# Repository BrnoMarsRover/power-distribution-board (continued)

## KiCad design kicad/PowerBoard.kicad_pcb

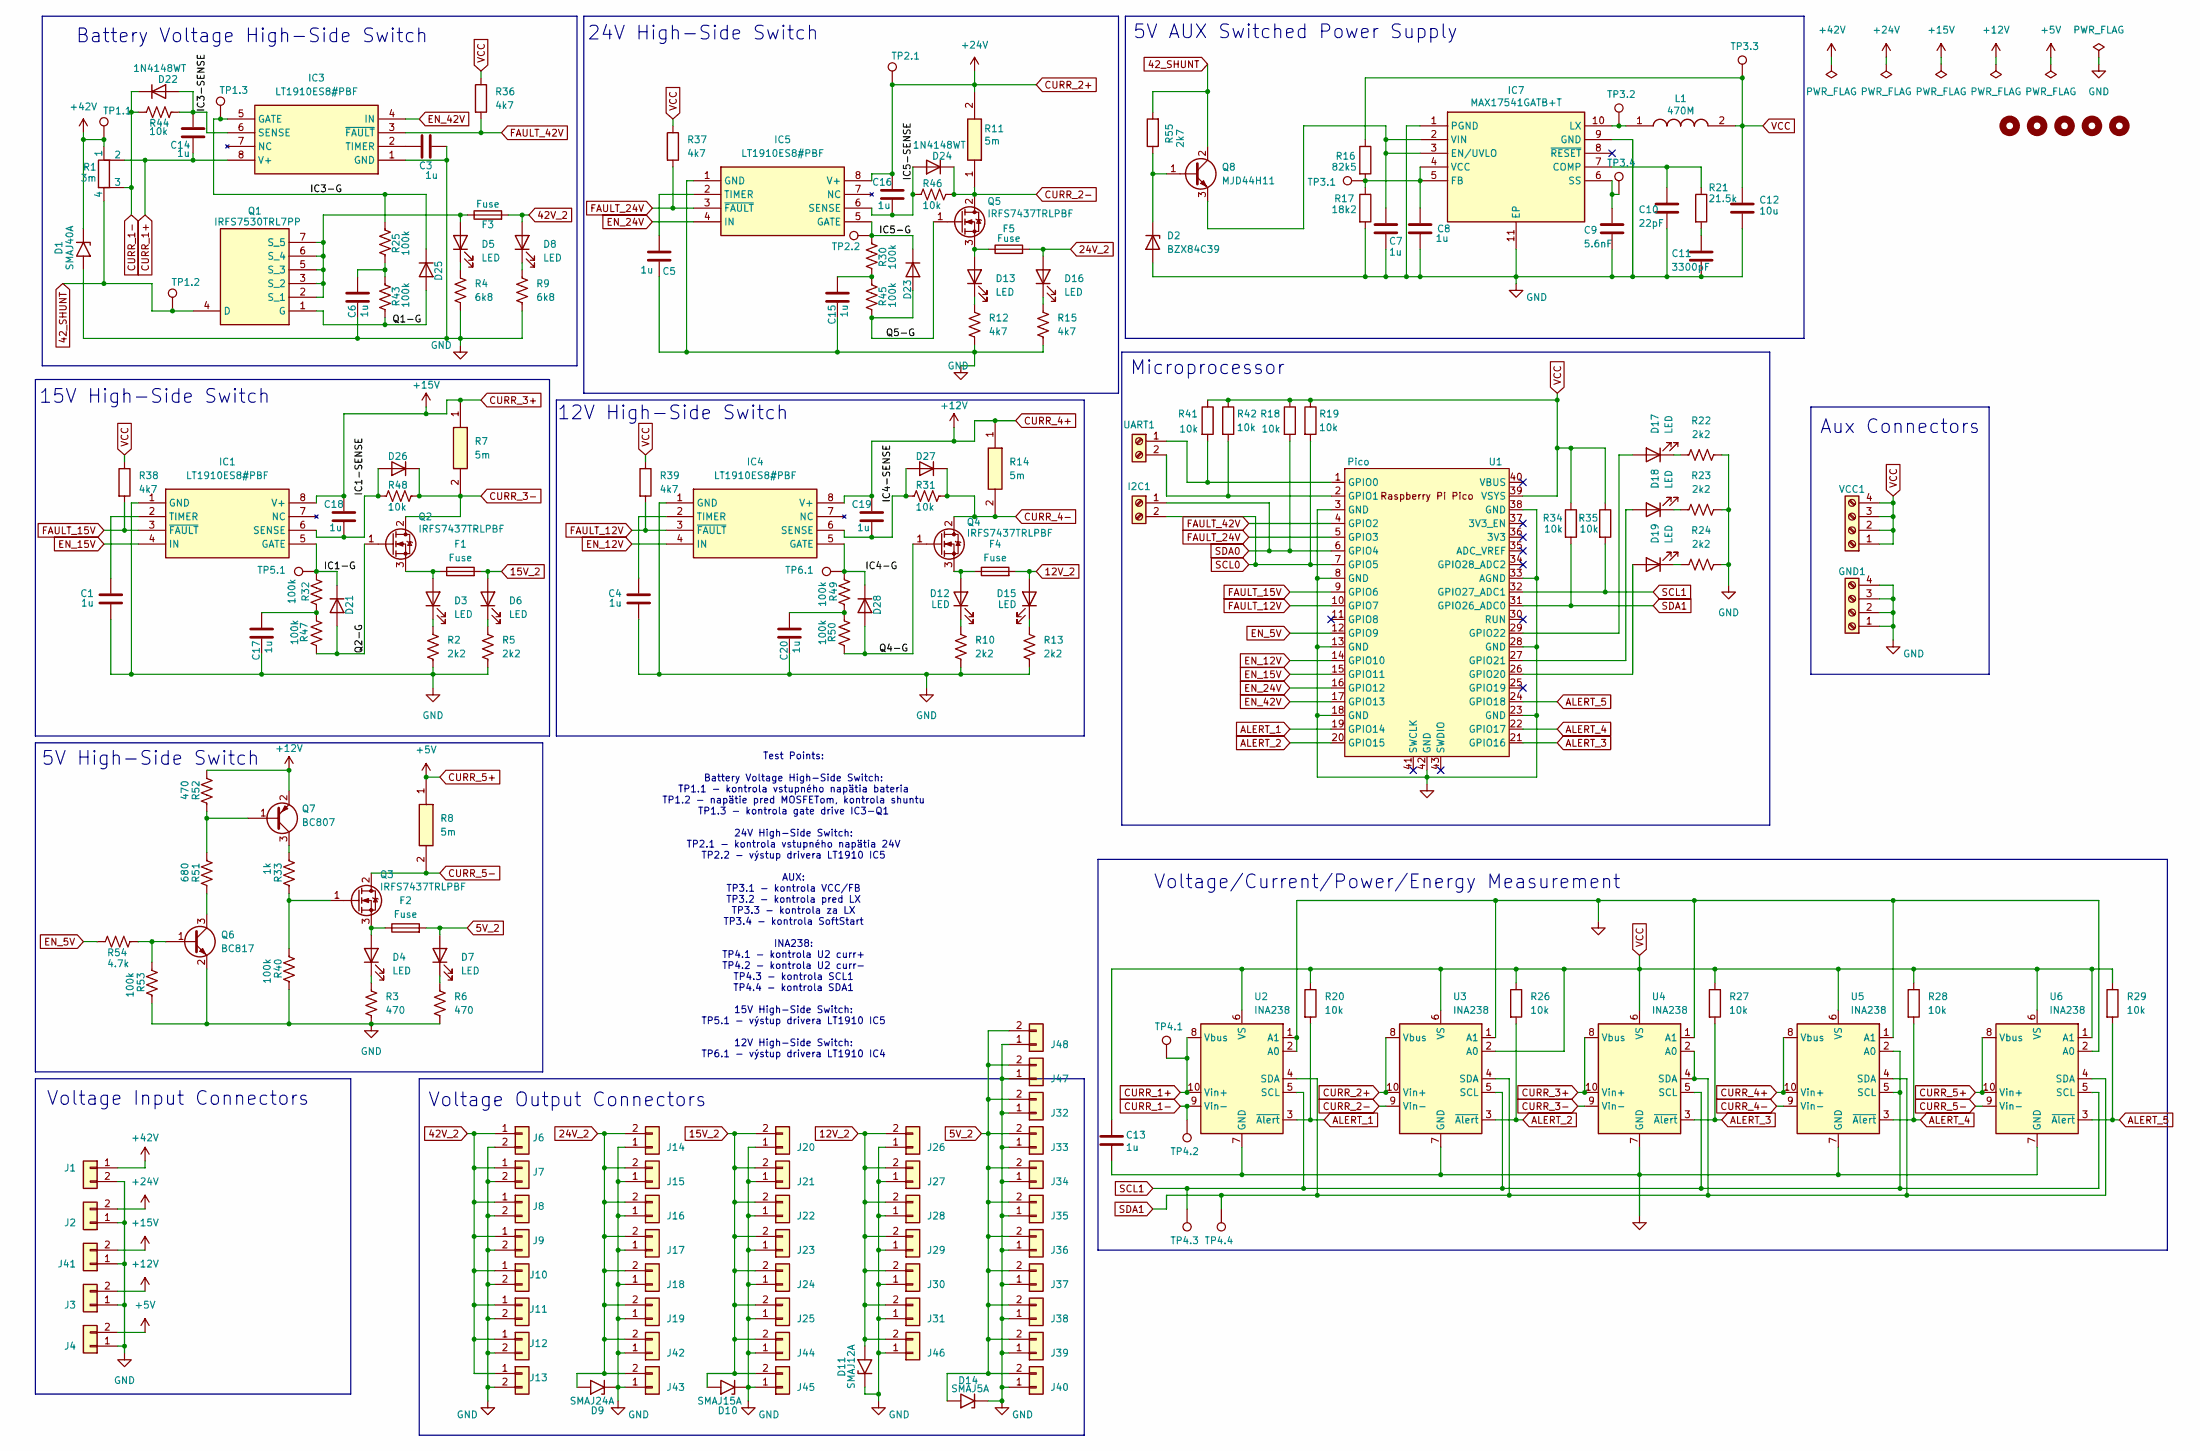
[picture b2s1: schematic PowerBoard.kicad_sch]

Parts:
C1, C3, C4, C5, C6, C7, C8, C14, C15, C16, C17, C18, C19, C20: 1u; C_0603_1608Metric
C9: 5.6nF; C_0603_1608Metric
C10: 22pF; C_0603_1608Metric
C11: 3300pF; C_0603_1608Metric
C12: 10u; C_0603_1608Metric
C13: 1u; C_1206_3216Metric
D1: SMAJ40A; D_SMA
D2: BZX84C39; SOT-23
D3, D4, D5, D6, D7, D8, D12, D13, D15, D16, D17, D18, D19: LED; D_1206_3216Metric
D9: SMAJ24A; D_SMA
D10: SMAJ15A; D_SMA
D11: SMAJ12A; D_SMA
D14: SMAJ5A; D_SMA
D21, D22, D23, D24, D25, D26, D27, D28: 1N4148WT; D_SOD-523
F1, F2, F3, F4, F5: Fuse; Fuse_Blade_ATO_directSolder
GND1: Screw_Terminal_01x04; TerminalBlock_Xinya_XY308-2.54-4P_1x04_P2.54mm_Horizontal
H1, H2, H3, H4, H5: MountingHole; MountingHole_3.2mm_M3
I2C1: Screw_Terminal_01x02; TerminalBlock_Xinya_XY308-2.54-2P_1x02_P2.54mm_Horizontal
IC1, IC3, IC4, IC5: LT1910ES8#PBF; SOIC127P599X175-8N; Mouser Part Number 584-LT1910ES8#PBF
IC7: MAX17541GATB+T; SON50P200X300X80-11N; Mouser Part Number 700-MAX17541GATB+T
J1, J6, J7, J8, J9, J10, J11, J12, J13: XT90
J2, J14, J15, J16, J17, J18, J19, J42, J43: DEAN_T; DEANS-T
J3, J20, J21, J22, J23, J24, J25, J26, J27, J28, J29, J30, J31, J41, J44, J45, J46: XT60; AMASS_XT60-F_1x02_P7.20mm_Vertical
J4, J32, J33, J34, J35, J36, J37, J38, J39, J40, J47, J48: XT30; AMASS_XT30U-F_1x02_P5.0mm_Vertical
L1: 470M; SRR5828A2R6Y; Mouser Part Number 6521-SRR5828A-470M
Q1: IRFS7530TRL7PP; Mouser Part Number 942-IRFS7530TRL7PP
Q2, Q3, Q4, Q5: IRFS7437TRLPBF; TO-263-2
Q6: BC817; SOT-23
Q7: BC807; SOT-23
Q8: MJD44H11; TO-252-2
R1: 3m; R_Shunt_Isabellenhuette_BVR4026
R2, R10: 2k2; R_0603_1608Metric
R3, R52: 470; R_0603_1608Metric
R4: 6k8; C_0603_1608Metric
R5, R13, R22, R23, R24: 2k2; R_1206_3216Metric
R6: 470; R_1206_3216Metric
R7, R8, R11, R14: 5m; RESC3216X89N; Mouser Part Number 71-WSL12061L000FEA
R9: 6k8; R_1206_3216Metric
R12: 4k7; R_0603_1608Metric
R15, R36, R37, R38, R39: 4k7; R_1206_3216Metric
R16: 82k5; R_0603_1608Metric
R17: 18k2; R_0603_1608Metric
R18, R19, R20, R26, R27, R28, R29, R34, R35, R41, R42: 10k; R_1206_3216Metric
R21: 21.5k; R_0603_1608Metric
R25, R30, R32, R40, R43, R45, R47, R49, R50, R53: 100k; R_0603_1608Metric
R31, R44, R46, R48: 10k; R_0603_1608Metric
R33: 1k; R_0603_1608Metric
R51: 680; R_0603_1608Metric
R54: 4.7k; R_0603_1608Metric
R55: 2k7; R_1206_3216Metric
TP1.1, TP1.2, TP1.3, TP2.1, TP2.2, TP3.1, TP3.2, TP3.3, TP3.4, TP4.1, TP4.2, TP4.3, TP4.4, TP5.1, TP6.1: TestPoint; TestPoint_Pad_1.0x1.0mm
U1: Pico; RPi_Pico_SMD_TH
U2, U3, U4, U5, U6: INA238; VSSOP-10_3x3mm_P0.5mm
UART1: Screw_Terminal_01x02; TerminalBlock_Xinya_XY308-2.54-2P_1x02_P2.54mm_Horizontal
VCC1: Screw_Terminal_01x04; TerminalBlock_Xinya_XY308-2.54-4P_1x04_P2.54mm_Horizontal

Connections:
5V_2: D7.2 (A), D14.2 (A2), F2.2, J32.2, J33.2, J34.2, J35.2, J36.2, J37.2, J38.2, J39.2, J40.2, J47.2, J48.2
12V_2: D11.2 (A2), D15.2 (A), F4.2, J26.2, J27.2, J28.2, J29.2, J30.2, J31.2, J46.2
15V_2: D6.2 (A), D10.2 (A2), F1.2, J20.2, J21.2, J22.2, J23.2, J24.2, J25.2, J44.2, J45.2
24V_2: D9.2 (A2), D16.2 (A), F5.2, J14.2, J15.2, J16.2, J17.2, J18.2, J19.2, J42.2, J43.2
42V_2: D8.2 (A), F3.2, J6.1, J7.1, J8.1, J9.1, J10.1, J11.1, J12.1, J13.1
42_SHUNT: Q1.4 (D), Q8.2 (C), R1.4, R55.2, TP1.2.1
+42V: D1.1 (A1), J1.1, R1.1, TP1.1.1
/IC1-G: D21.1 (K), IC1.5 (GATE), R32.2, TP5.1.1
/IC1-SENSE: C18.2, D26.2 (A), IC1.6 (SENSE), R48.1
/IC3-G: D25.1 (K), IC3.5 (GATE), R25.2, TP1.3.1
/IC3-SENSE: C14.1, D22.2 (A), IC3.6 (SENSE), R44.2
/IC4-G: D28.1 (K), IC4.5 (GATE), R49.2, TP6.1.1
/IC4-SENSE: C19.2, D27.2 (A), IC4.6 (SENSE), R31.1
/IC5-G: D23.1 (K), IC5.5 (GATE), R30.2, TP2.2.1
/IC5-SENSE: C16.2, D24.2 (A), IC5.6 (SENSE), R46.1
/Q1-G: D25.2 (A), Q1.1 (G), R43.2
/Q2-G: D21.2 (A), Q2.1 (G), R47.2
/Q4-G: D28.2 (A), Q4.1 (G), R50.2
/Q5-G: D23.2 (A), Q5.1 (G), R45.2
ALERT_1: R20.2, U1.19 (GPIO14), U2.3 (~Alert)
ALERT_2: R26.2, U1.20 (GPIO15), U3.3 (~Alert)
ALERT_3: R27.2, U1.21 (GPIO16), U4.3 (~Alert)
ALERT_4: R28.2, U1.22 (GPIO17), U5.3 (~Alert)
ALERT_5: R29.2, U1.24 (GPIO18), U6.3 (~Alert)
CURR_1+: C14.2, IC3.8 (V+), R1.2, TP4.1.1, U2.8 (Vbus), U2.10 (Vin+)
CURR_1-: D22.1 (K), R1.3, R44.1, TP4.2.1, U2.9 (Vin-)
CURR_2+: C16.1, IC5.8 (V+), J2.2, R11.2, TP2.1.1, U3.8 (Vbus), U3.10 (Vin+)
CURR_2-: D24.1 (K), Q5.2 (D), R11.1, R46.2, U3.9 (Vin-)
CURR_3+: C18.1, IC1.8 (V+), J41.2, R7.1, U4.8 (Vbus), U4.10 (Vin+)
CURR_3-: D26.1 (K), Q2.2 (D), R7.2, R48.2, U4.9 (Vin-)
CURR_4+: C19.1, IC4.8 (V+), J3.2, Q7.2 (E), R14.1, R52.2, U5.8 (Vbus), U5.10 (Vin+)
CURR_4-: D27.1 (K), Q4.2 (D), R14.2, R31.2, U5.9 (Vin-)
CURR_5+: J4.2, R8.1, U6.8 (Vbus), U6.10 (Vin+)
CURR_5-: Q3.2 (D), R8.2, U6.9 (Vin-)
EN_5V: R54.2, U1.12 (GPIO9)
EN_12V: IC4.4 (IN), U1.14 (GPIO10)
EN_15V: IC1.4 (IN), U1.15 (GPIO11)
EN_24V: IC5.4 (IN), U1.16 (GPIO12)
EN_42V: IC3.4 (IN), U1.17 (GPIO13)
FAULT_12V: IC4.3 (~FAULT), R39.2, U1.10 (GPIO7)
FAULT_15V: IC1.3 (~FAULT), R38.2, U1.9 (GPIO6)
FAULT_24V: IC5.3 (~FAULT), R37.2, U1.5 (GPIO3)
FAULT_42V: IC3.3 (~FAULT), R36.2, U1.4 (GPIO2)
GND: C1.2, C3.2, C4.2, C5.2, C6.1, C7.2, C8.2, C9.2, C10.2, C11.2, C12.2, C13.2, C15.1, C17.1, C20.1, D1.2 (A2), D2.1 (A), D9.1 (A1), D10.1 (A1), D11.1 (A1), D14.1 (A1), GND1.1, GND1.2, GND1.3, GND1.4, IC1.1 (GND), IC3.1 (GND), IC4.1 (GND), IC5.1 (GND), IC7.1 (PGND), IC7.9 (GND), IC7.11 (EP), J1.2, J2.1, J3.1, J4.1, J6.2, J7.2, J8.2, J9.2, J10.2, J11.2, J12.2, J13.2, J14.1, J15.1, J16.1, J17.1, J18.1, J19.1, J20.1, J21.1, J22.1, J23.1, J24.1, J25.1, J26.1, J27.1, J28.1, J29.1, J30.1, J31.1, J32.1, J33.1, J34.1, J35.1, J36.1, J37.1, J38.1, J39.1, J40.1, J41.1, J42.1, J43.1, J44.1, J45.1, J46.1, J47.1, J48.1, Q6.2 (E), R2.2, R3.2, R4.2, R5.2, R6.2, R9.2, R10.2, R12.2, R13.2, R15.2, R17.2, R22.2, R23.2, R24.2, R40.1, R53.1, U1.3 (GND), U1.8 (GND), U1.13 (GND), U1.18 (GND), U1.23 (GND), U1.28 (GND), U1.33 (AGND), U1.38 (GND), U1.42 (GND), U2.1 (A1), U2.2 (A0), U2.7 (GND), U3.1 (A1), U3.7 (GND), U4.1 (A1), U4.7 (GND), U5.1 (A1), U5.7 (GND), U6.2 (A0), U6.7 (GND)
unnamed: C6.2, R25.1, R43.1
unnamed: C11.1, R21.2
unnamed: C15.2, R30.1, R45.1
unnamed: C17.2, R32.1, R47.1
unnamed: C20.2, R49.1, R50.1
unnamed: D2.3 (K), Q8.1 (B), R55.1
unnamed: D3.2 (A), F1.1, Q2.3 (S)
unnamed: D3.1 (K), R2.1
unnamed: D4.2 (A), F2.1, Q3.3 (S)
unnamed: D4.1 (K), R3.1
unnamed: D5.2 (A), F3.1, Q1.2 (S_1), Q1.3 (S_2), Q1.5 (S_3), Q1.6 (S_4), Q1.7 (S_5)
unnamed: D5.1 (K), R4.1
unnamed: D6.1 (K), R5.1
unnamed: D7.1 (K), R6.1
unnamed: D8.1 (K), R9.1
unnamed: D12.2 (A), F4.1, Q4.3 (S)
unnamed: D12.1 (K), R10.1
unnamed: D13.2 (A), F5.1, Q5.3 (S)
unnamed: D13.1 (K), R12.1
unnamed: D15.1 (K), R13.1
unnamed: D16.1 (K), R15.1
unnamed: D17.2 (A), U1.29 (GPIO22)
unnamed: D17.1 (K), R22.1
unnamed: D18.2 (A), U1.27 (GPIO21)
unnamed: D18.1 (K), R23.1
unnamed: D19.2 (A), U1.26 (GPIO20)
unnamed: D19.1 (K), R24.1
unnamed: C1.1, IC1.2 (TIMER)
unnamed: C3.1, IC3.2 (TIMER)
unnamed: C4.1, IC4.2 (TIMER)
unnamed: C5.1, IC5.2 (TIMER)
unnamed: C10.1, IC7.7 (COMP), R21.1
unnamed: C7.1, IC7.2 (VIN), IC7.3 (EN/UVLO), Q8.3 (E)
unnamed: C8.1, IC7.4 (VCC), IC7.5 (FB), R16.2, R17.1, TP3.1.1
unnamed: IC7.10 (LX), L1.1, TP3.2.1
unnamed: C9.1, IC7.6 (SS), TP3.4.1
unnamed: Q3.1 (G), R33.1, R40.2
unnamed: Q6.1 (B), R53.2, R54.1
unnamed: Q6.3 (C), R51.1
unnamed: Q7.1 (B), R51.2, R52.1
unnamed: Q7.3 (C), R33.2
unnamed: R41.2, U1.1 (GPIO0), UART1.1
unnamed: R42.2, U1.2 (GPIO1), UART1.2
SCL0: I2C1.2, R19.2, U1.7 (GPIO5)
SCL1: R35.2, TP4.3.1, U1.32 (GPIO27_ADC1), U2.5 (SCL), U3.5 (SCL), U4.5 (SCL), U5.2 (A0), U5.5 (SCL), U6.5 (SCL)
SDA0: I2C1.1, R18.2, U1.6 (GPIO4)
SDA1: R34.2, TP4.4.1, U1.31 (GPIO26_ADC0), U2.4 (SDA), U3.4 (SDA), U4.2 (A0), U4.4 (SDA), U5.4 (SDA), U6.4 (SDA)
VCC: C12.1, C13.1, L1.2, R16.1, R18.1, R19.1, R20.1, R26.1, R27.1, R28.1, R29.1, R34.1, R35.1, R36.1, R37.1, R38.1, R39.1, R41.1, R42.1, TP3.3.1, U1.39 (VSYS), U2.6 (VS), U3.2 (A0), U3.6 (VS), U4.6 (VS), U5.6 (VS), U6.1 (A1), U6.6 (VS), VCC1.1, VCC1.2, VCC1.3, VCC1.4

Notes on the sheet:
12V High-Side Switch
24V High-Side Switch
Voltage/Current/Power/Energy Measurement
Aux Connectors
15V High-Side Switch
Microprocessor
Battery Voltage High-Side Switch
5V High-Side Switch
Test Points: Battery Voltage High-Side Switch: TP1.1 - kontrola vstupného napätia bateria TP1.2 - napätie pred MOSFETom, kontrola shuntu TP1.3 - kontrola gate drive IC3-Q1 24V High-Side Switch: TP2.1 - kontrola vstupného napätia 24V TP2.2 - výstup drivera LT1910 IC5 AUX: TP3.1 - kontrola VCC/FB TP3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
Voltage Output Connectors
Voltage Input Connectors
5V AUX Switched Power Supply

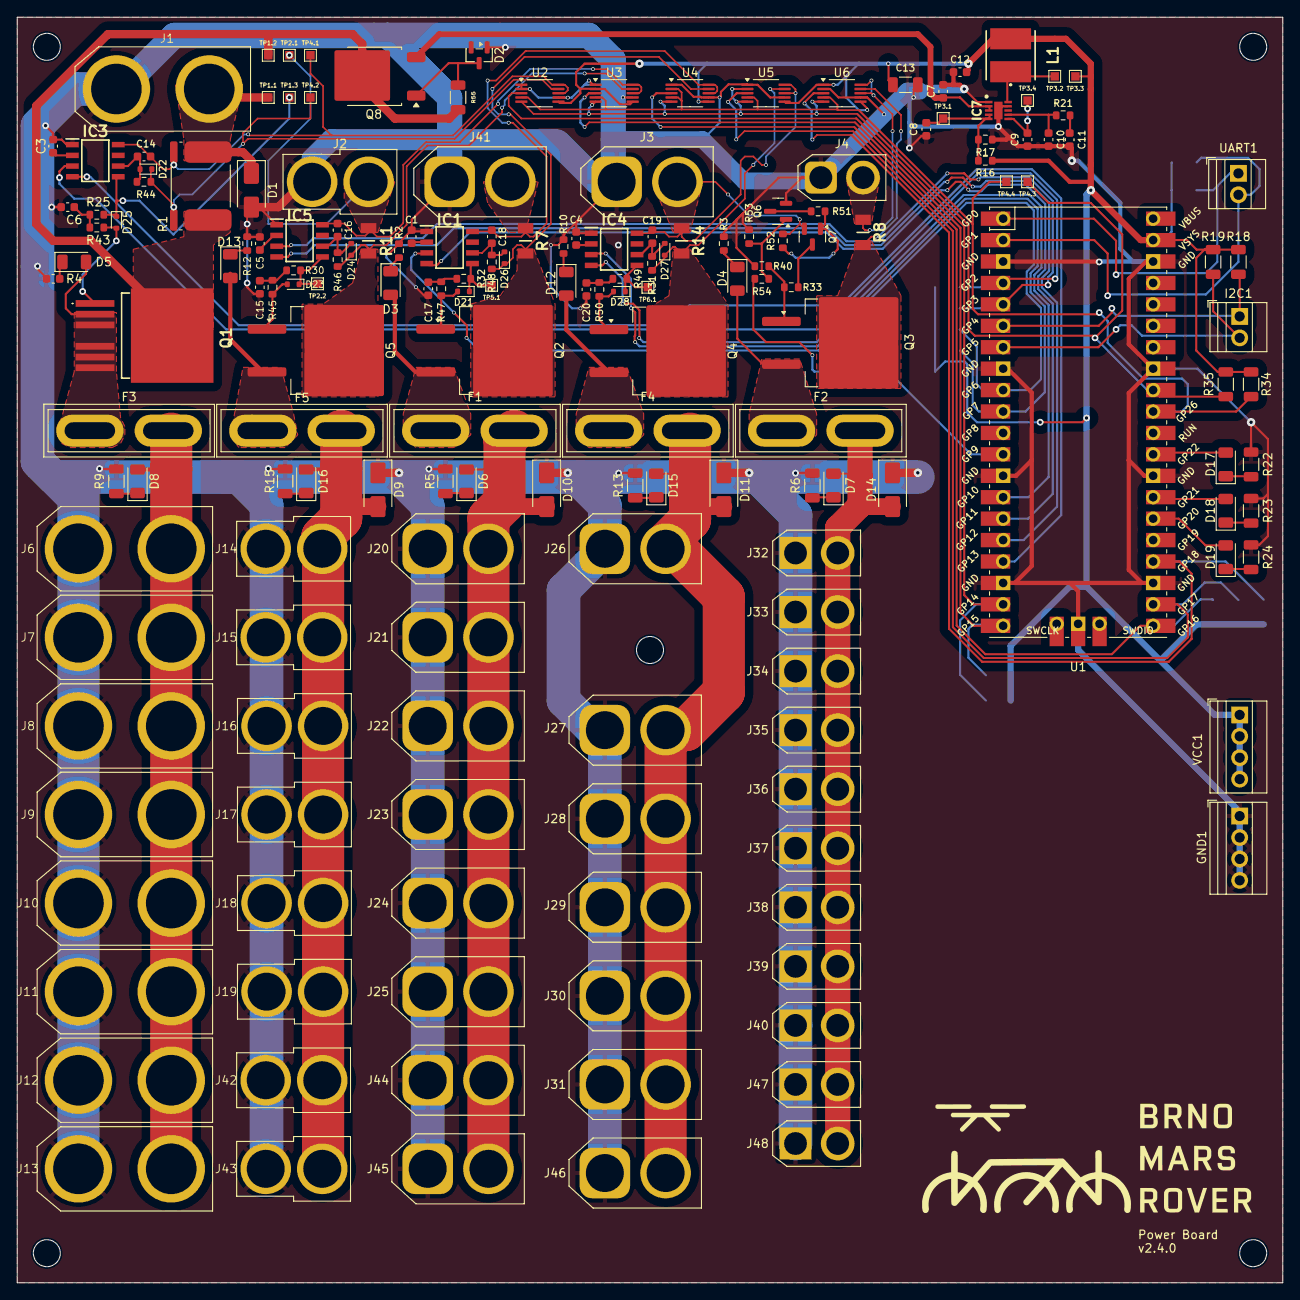
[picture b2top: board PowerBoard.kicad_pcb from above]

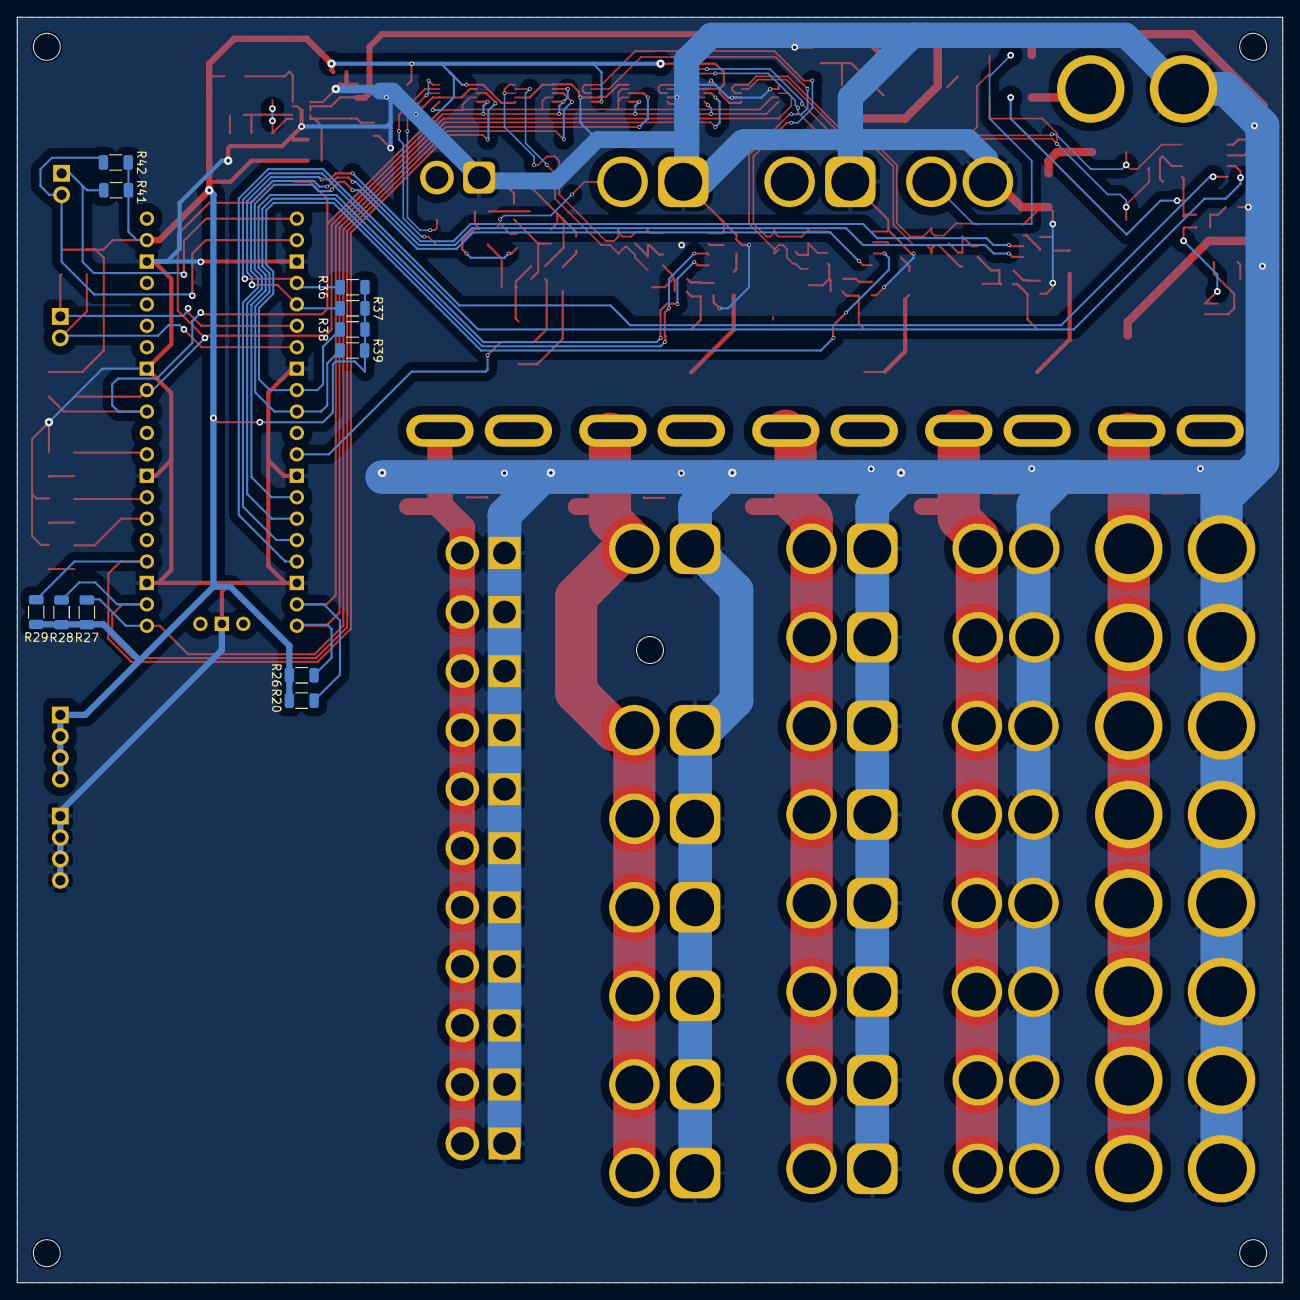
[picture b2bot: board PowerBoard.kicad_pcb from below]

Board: 2 copper layers, 150.0 x 150.0 mm, 197 parts (11 on the bottom side), 92 nets.

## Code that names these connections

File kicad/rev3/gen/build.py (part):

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    W(PIN(rgp, 2), PIN(cgp, 1))
    gnd(PIN(cgp, 2))
    W(PIN(rs, 4), (PIN(qp, 2)[0], yR))
    lab("L:DRN", (PIN(rs, 4)[0] + 5.08, yR), 0)        # named so board netclasses can find it

    # --- emergency bypass: solder a short solid-copper wire bridge across these two holes to power
    # the output with this eFuse out of the loop. After the shunt, so IMON still reads.
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    # resistor connector with the freewheel diode across it
    ysw = 96.52
    W(PIN(q, 2), (PIN(q, 2)[0], ysw), (157.48, ysw), (157.48, y0 + 2.54), (162.56, y0 + 2.54))
    lab("L:BRK_SW", (PIN(q, 2)[0] + 1.27, ysw), 0)    # named so the board netclass can find it
    j = CONN2(sh, "XT60PT-F (brake resistor)", "XT60F", "OUT42D", "L:BRK_SW")
    at_pin(j, 1, (162.56, y0))
    j.label_at = {"Reference": (2.54, 0), "Value": (2.54, 2.54)}
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    W((P(5)[0], 106.68), (86.36, 106.68))
    hang(sh, C(sh, 1e-6, "L:VIN_LM", "GND", fp="C1206", volt=100, rot=0), (86.36, 106.68))
    sh.mark("flag", (90.17, 106.68))
    rcp = hang(sh, R(sh, 100, "OUT42C", "L:CSP", rot=0), PIN(rs, 1), gap=7.62, gnd=False)
    rcn = hang(sh, R(sh, 100, "L:LIN", "L:CSN", rot=0), PIN(rs, 2), gap=7.62, gnd=False)
    ccs = C(sh, 1e-9, "L:CSP", "L:CSN")
    at_pin(ccs, 1, (P(4)[0], 106.68))
    W(PIN(rcp, 2), P(4))
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    W(PIN(rut, 2), (22.86, P(6)[1]), PIN(q_en, 3))
    gnd(PIN(q_en, 2))
    W(PIN(q_en, 1), (5.08, PIN(q_en, 1)[1]))
    lab("BOOST_DIS", (5.08, PIN(q_en, 1)[1]), 180)
    rpu = R(sh, 100e3, "+3V3", "BOOST_DIS", rot=0)
    at_pin(rpu, 2, (10.16, PIN(q_en, 1)[1]))
    v33(PIN(rpu, 1))
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    return sh


ESP_PINS = {"1": "GND", "2": "+3V3", "3": "ESP_EN", "4": "I2C_SDA", "5": "I2C_SCL", "6": "FLT_42D",
            "7": "FLT_42C", "8": "UART_SP", "9": "FLT_5", "10": "UART_RX", "11": "FLT_24", "12": "UART_TX",
            "13": "USB_DN", "14": "USB_DP", "15": None, "16": None, "17": "FLT_12", "18": "INA_ALERT",
            "19": "CAN_STB", "20": "CAN_TXD", "21": "CAN_RXD", "22": None, "23": "LED_1",
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    xg = x0 + 50.8
    at_pin(gh, 1, (xg, yt))
    gh.label_at = {"Reference": (3.81, -5.08), "Value": (3.81, -2.54)}
    lab("L:RX_C", PIN(e2, 6), 0)
    lab("L:TX_C", PIN(e2, 4), 0)
    lab("L:TX_C", PIN(gh, 1), 180)
    lab("L:RX_C", PIN(gh, 2), 180)
    W(PIN(gh, 3), (xg - 5.08, yt + 5.08), (xg - 5.08, yt + 15.24))
    gnd((xg - 5.08, yt + 15.24))
    rsp = R(sh, 1e3, "L:SP_C", "UART_SP", rot=0)
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    P = lambda n: PIN(U, n)

    # logic side from the ESP32
    for pin_, net in ((1, "CAN_TXD"), (4, "CAN_RXD"), (8, "CAN_STB")):
        W(P(pin_), (73.66, P(pin_)[1]))
        lab(net, (73.66, P(pin_)[1]), 180)
    gnd(P(2))
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# unused ADC inputs are tied to GND, the expander pins left open like the other spares.
ADC_MAP = [["IMON_42D", "IMON_42C", "IMON_24", "IMON_12", "IMON_5", "GND", "VSNS_OUT_42D", "VSNS_OUT_42C"],
           ["VSNS_OUT_24", "VSNS_OUT_12", "VSNS_OUT_5", "VSNS_OUT_54", "VSNS_IN_24", "VSNS_IN_12", "VSNS_IN_5", "GND"]]
# INPG_42C and INP_42D swapped 2026-11-24 (P00 / P07), so the 42 V far end reaches the expander in pin order with no
# L3 hops in the 5 V output's current (far42.py)
EXP_MAP = {4: "INPG_42C", 5: "INP_42C", 6: "INP_24", 7: "INP_12", 8: "INP_5", 9: None, 10: "INPG_42D",
           11: "INP_42D", 13: "INPG_24", 14: "INPG_12", 15: "INPG_5", 16: None, 17: "MOTOR_ARM",
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        "It stays off after the switch closes until the ESP32 clocks MOTOR_ARM, which it does only after dropping INP and "
        "re-running pre-charge. Power-on also starts latched off. The battery E-STOP is separate (BMS soft-start).",
        "Soft power: the BMS soft-start loop (through the E-STOP) is closed by button pole 1 or by the AQY282S that the ESP32 "
        "holds (PWR_HOLD, GPIO40). Pole 2 reads the button (PWR_BTN, GPIO41, low = on). Button off: the ESP32 asks the "
        "Jetson to stow and shut down, then releases PWR_HOLD. A reset or a dead ESP32 releases it too."],
        drawn=True)
    W, gnd, v33, lab = marks(sh)
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
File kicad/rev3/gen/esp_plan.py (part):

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U15's connector-side pins 4 / 6 go straight up to J33's pins 1 / 2 (0.4 mm, the discharge's path), its supply pin
to a +3V3 via between them, its GND pin to a via below it.

The north bundle (decided 2026-11-22: MOTOR_OK moved to pin 35): PWR_HOLD, MOTOR_OK and the power button's sense line
leave the module's bottom row together (pins 33, 35; PWR_BTN's pin 34 goes through its RC filter R175 / C120, placed
right there, so the bundle's third line is BTN_SNS) and run on L3 as one bundle to the top-right corner:

  vias inside the module's bottom edge -> nested runs east under the module -> north up the board's right side
  (right of the I2C path, under U12 and the aux diodes) -> a jog right past the aux supply's GND via -> north right
  of J33's, J36's pins -> west between J36 and J37 into the corner, each line peeling off in order:
  BTN_SNS north into J37's pin 3 (through-hole), MOTOR_OK to a via at R167, PWR_HOLD to vias at R172 and R173.

KEEP_TOP: the band above the module's top pin row (its pins' escapes: the FLT bus's pin vias and these lines) and
the resistors with their tracks; KEEP_BOTTOM: the vias south of U15, in the aux network's pocket.
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COL_X = {"PWR_HOLD": 146.3, "MOTOR_OK": 146.8, "BTN": 147.3}      # north under the module's right side
JOG_Y, JOG_DX = {"PWR_HOLD": 45.3, "MOTOR_OK": 45.6, "BTN": 45.9}, 1.3   # right, past the aux GND via (148.2, 46.23)
WEST_Y = {"PWR_HOLD": 18.4, "MOTOR_OK": 17.5, "BTN": 16.6}        # west between J36 and J37 (0.9 pitch: vias)
R175_C, C120_C = (143.6, 75.5), (143.6, 73.4)    # PWR_BTN's RC at its pin (bottom side), the PWR_BTN pads left
BTN_DETOUR_Y = 77.75                             # PWR_BTN: under the pin row, past MOTOR_OK's via, up to the RC
C120_GND_VIA = (145.4, 72.9)
import corner_plan                                # the bundle's corner ports: corner_plan lays the rest (by hand)
PORT_X = corner_plan.PORT_X
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        power42._upright(FP[ref], px, RES_Y, other, mcu, bottom=False)
        FP[ref].SetLocked(True)
        done.append(ref)
    # PWR_BTN's RC filter at its pin (bottom side, under the module): R175 (to the sense line) and C120
    from i2c_plan import _flat_b
    from satellites import _box
    r175 = next(r for r, f in FP.items() if r.startswith("R") and "PWR_BTN" in {p.GetNetname() for p in f.Pads()})
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        turn = [(fx, y + 0.5), (fx + 0.5, y)] if fy - y > 0.6 else [(fx + (fy - y), y)]
        lay(side, F, [(fx, fy)] + turn + [(vx, y)])
        via(side, vx, y)
        if net == "UART_SP":                                      # L3 to J33's pin 4
            jx, jy = j33["4"]["c"]
            x0, y1, x2 = SP_COL                                   # north, north-east past U15, north to the pin
            lay(side, IN2, [(vx, y), (x0, y1), (x2, y1 - (x2 - x0)), (x2, jy + 2.0),
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    btn = next(q["net"] for q in R.geo.pads if q["ref"] == r175 and q["net"] != "PWR_BTN")
    nets = {"PWR_HOLD": "PWR_HOLD", "MOTOR_OK": "MOTOR_OK", "BTN": btn}
    c120 = next(q["ref"] for q in R.geo.pads if q["net"] == "PWR_BTN" and q["ref"].startswith("C"))
    # the module end: PWR_HOLD / MOTOR_OK pins to vias inside the edge; PWR_BTN's pin to its via, under the pin row
    # to its RC; the sense line from R175 to its via
    start = {}
    for key in ("PWR_HOLD", "MOTOR_OK"):
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# ---- the group's own nets (pcb_route.py espnet, after the switch-control group): planned escapes, then the router
ESC_LEFT_X, ESC_BOTTOM_Y = 131.6, 80.4           # the left column's vias just inside the edge, the bottom row's outside
LEFT_PINS = ("19", "20", "21", "23", "24", "25")  # CAN x3, LED x3
BOTTOM_PINS = ("31", "36", "37", "38", "39")      # spare, RXD0, TXD0, AUX5 and NTC sense (32 BRAKE_ACT: its own plan)
IO0_VIA = (130.1, 80.4)                          # IO0: beside pin 27, a top-side stub on to the BOOT switch
EN_VIA, EN_SW_VIA = (145.38, 62.55), (136.9, 84.5)   # EN: under the module edge; at the RESET switch (under its body)
V3_VIA = (148.08, 63.05)                          # +3V3: pin 2 east under the module edge, right of the north
GND_VIAS = {"1": (148.08, 61.9), "40": (147.92, 80.4)}   # bundle's L3 columns, then a bottom stub to U12's tab
KEEP_ESC = [(130.95, 67.2, 132.25, 76.2), (129.45, 79.75, 147.5, 81.05), (136.25, 83.85, 137.55, 85.15)]
# BRAKE_ACT (pin 32) to the brake comparator in the bottom-left corner, about 170 mm on L3, all planned: south beside
# the ESP32's group (east of the I2C trunk's end), west in the one long free L3 lane, between output rows 2 and 3
# (y 101.4, BOOST_DIS beside it at y 102.0, boost_plan), down the 42D plane's east edge and beside the switch-node
# shield (BOOST_DIS east of it), west above the comparator's south row to a via between its status divider's
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

def brake(R, FP, log=print):
    """BRAKE_ACT: pin 32's escape and the planned L3 run to the comparator's status divider."""
    import route_plan
    import far42
    from route import B, F, IN2
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#    (between the DP / DN exits) and L3 to the north VBUS via;
#  - both VBUS pads joined on L3, under the pad column;
#  - GND pads into the shield tabs (top side; the tabs are plated through to the GND plane);
#  - USB_DP / USB_DN: the module's pins 14 / 13 to vias under its corner, the router from there to U14's pins 4 / 6.
# VBUS_USB on to the OR diode D17: since 2026-11-23 D17 sits just south of the receptacle (logic5v).
USB_J32 = {"A9": (142.645, 84.365), "B5": (142.645, 85.015), "B6": (142.645, 86.015), "A7": (142.645, 86.515),
           "A6": (142.645, 87.015), "B7": (142.645, 87.515), "A5": (142.645, 88.015), "A4": (142.645, 89.165),
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# USB_DP / USB_DN as a pair on the bottom side, 0.5 mm apart (DN on the east side): from the module's vias south-east
# between the left-column escapes and R156, south west of the module's decap C105 (crossing the I2C rows, never
# along an L3 line), south-east under the module's bottom row, west of the PWR_HOLD via, through the escape row east
# of BRAKE_ACT's via, then DP west and DN east round U14's VBUS via into pins 4 / 6
USB_DP_PATH = [(131.75, 64.15), (131.75, 64.81), (134.9, 67.96), (134.9, 73.3), (137.4, 75.8), (137.4, 77.5),
               (138.6, 78.7), (138.6, 84.0), (137.8, 84.8), (137.8, 86.5)]
USB_DN_PATH = [(132.9, 64.6), (132.9, 65.253), (135.4, 67.753), (135.4, 73.093), (137.9, 75.593), (137.9, 77.293),
               (139.1, 78.493), (139.1, 84.0), (139.7, 84.6), (139.7, 86.5)]
# MOTOR_OK's latch side (C114 / D21 / R169, west of the module) to pin 35: on the top side, from pin 35's pad south and
# west along the module's south edge (between the bottom row's escape vias and the BOOT / RESET pads) to a via by
# BOOT; the router (switch control) takes it on from there. So it crosses neither the USB pair nor the I2C lines
MOK_LANE_Y = 81.3
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
# the ESP32 support group's small parts, frozen where the packer had put them on 2026-11-22 (reviewed and routed
# that way: USB, LEDs, EN / IO0, NTC, AUX5, CC). Its packer re-shuffles them whenever anything near the module
# changes (2026-11-23: the CAN pin swap put R162 across the CAN lines and C105 on USB_DN). ref: (x, y, deg, nets)
SUPPORT = {"C104": (143.35, 68.289, 0.0, "+3V3 GND"),    # (the aux sheet's spare +3V3 cap, packed with these)
           "C105": (136.657, 70.027, -90.0, "+3V3 GND"), "C106": (147.254, 68.277, 0.0, "+3V3 GND"),
           "C107": (135.62, 87.463, -90.0, "ESP_EN GND"), "C108": (147.901, 73.65, -90.0, "NTC_SNS GND"),
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

def motor_ok_link(R, log=print):
    """MOTOR_OK's top-side lane from pin 35 to its via by BOOT (the switch-control group routes the rest)."""
    import far42
    import route_plan
    from route import F
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
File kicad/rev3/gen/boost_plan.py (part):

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  HO        leaves between C78's pads (0.2 mm neck), north outside SW and into Q24's gate lead from below.
  BST       into C78's BST pad, on to D13's cathode.
  GND       pins 13 / 15 (and 2 / 9) tie into the exposed pad; C79's GND pad has its own via.
  FB feed   R130 (the divider's top, at the FB pin) gets OUT54 from a via in the slot between Q24's gate lead and
            its tab, on L3 west, north of LO's run; the router finishes it at R130.

Laid after the power copper (key "boost"), as planned polylines checked exactly; the router then takes the loop
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            (14.5, 144.6, 27.6, 147.0), (28.3, 122.5, 31.6, 124.1)]

# ---- the corner's last parts and nets (decided 2026-11-22)
# BOOST_DIS: the expander's pin 18 (U17, under the 12 V outputs) to the UVLO pull-down Q25 in the corner, ~130 mm, a
# DC line. U17's pocket is closed on L3 (the I2C trunk, MOTOR_ARM's hop), so: a via beside pin 18 (in route_plan's
# U17_ESC_KEEP), L3 south-west beside I2C_SCL's diagonal to a via above the 12 V XT60 J20, the bottom side down
# between J20 / J21's left pins and I2C_SDA's hop vias, L3 again west along y 102.0 beside BRAKE_ACT (y 101.4,
# esp_plan) and down the corner with it, east of it: down the 42D plane's east edge, down beside the switch-node
# shield, west under the comparator's south edge (BRAKE_ACT turns west above the comparator's IC), down between the
# brake FET's gate via and R130's OUT54 via to a via under Q25. The pull-up R135 sits on the bottom-side column below
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
# ---- the brake comparator (decided 2026-11-22, by hand; the packer had IN+ / IN- parts on the wrong sides of U8).
# U8 (TLV1805, bottom) keeps its pins: inputs on top (IN- left, IN+ right), OUT bottom-left, V+ bottom-right. The IN+
# network (R115 from OUT42D, which taps the brake XT60's OUT42D pin right above it, R116 to GND, R117 from OUT) stands
# north of U8, OUT goes west to the gate resistor R118 and the gate via, V+ east to its cap C71, the zener D11 and the
# feed R112 / R113. OUT-to-IN+ and V+-to-IN- cross; IN- (the LM4040's low-impedance node) takes the gap between U8's
# pin columns, south to U9 and R114. BRAKE_ACT's status divider (R119 from the gate, R120 to GND) at the west edge.
# BRAKE_ACT (L3, esp_plan) crosses west above U9 at y 129.9, BOOST_DIS (L3) under the south row at y 133.15: no vias
# in those bands. Spec: (nets: top / left pad first), centre, upright?
CMP_IC = {"U8": (9.0, 127.45, 0), "U9": (8.745, 131.5, 180)}
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    j4 = min((q for q in R.geo.pads if short(q) == "OUT42D" and q["ref"].startswith("J")
              and q["box"][0] < o[0] < q["box"][2] and q["box"][3] < o[1]), key=lambda q: o[1] - q["box"][3])
    c = lambda ref, n: P(ref, n)["c"]
    # OUT42D: R115 straight up into the brake XT60's OUT42D pin
    jc = j4["c"]                                       # (the pin's pad is round: end at its centre)
    yb = jc[1] + (jc[0] - o[0])
    lay(P(r115, "OUT42D")["net"], [o, (o[0], yb), jc], 0.5)
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
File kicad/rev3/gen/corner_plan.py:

"""The power-button corner (top right), by hand (decided 2026-11-23).

The parts: the PhotoMOS U22 (the ESP32's hold on the BMS soft-start pair, parallel to the button's pole 1), its LED
resistor R172 and PWR_HOLD's pull-down R173; the button sense's pull-up R174; the motor switch loop's input
resistors (R166 from +3V3 into J36.1, R168 from J36.2 to GND, R167 from J36.2 to MOTOR_OK). The connectors: J37 (the
button: SS_A, SS_B, BTN_SNS, GND), J38 (the BMS soft-start pair, through the E-STOP) and J36 (the motor switch loop),
all through-hole. The north bundle (esp_plan) brings PWR_HOLD, MOTOR_OK and BTN_SNS west on L3 between J37 and J36.

  soft-start  J38 to J37 on the top side (through-hole to through-hole, clear of everything on the bottom); U22's
              output pins (3 SS_A above 4 SS_B, facing east) to J37: SS_A along the bottom side, SS_B through a via
              and along the top side (U22's pin order would make the two cross on one layer)
  PWR_HOLD    the bundle's port moves west, above U22: a via there, the bottom side north to R172 (on to U22's LED
              anode) with R173 to GND on the way
  MOTOR_OK    the port moves east, beside J36: R167 (MOTOR_OK west, the loop node east) right above J36's pin 2,
              R168 above it into J37's GND pin, R166 west of J36 (its +3V3 via below it, out of the bundle's band)
  BTN_SNS     R174 right above J37's pin 3, its +3V3 via beside it (BTN_SNS reaches pin 3 on L3, esp_plan)

No via goes in the bundle's L3 band (y 15.9 ... 19.1) east of the ports. Laid in the ESP32 group's stage, after the
bundle (pcb_route esp, esp_plan.corner), as planned polylines checked exactly.
"""
W, W_SS = 0.25, 0.4
PORT_X = {"MOTOR_OK": 143.9, "PWR_HOLD": 131.0}          # (esp_plan.PORT_X: the bundle's L3 lines end here)
# (nets: first one up / west), centre, upright?
PARTS = [(("+3V3", "Net-(J36-Pin_1)"), (140.6, 22.6), False),       # R166
         (("MOTOR_OK", "Net-(J36-Pin_2)"), (145.0, 19.0), False),   # R167
         (("GND", "Net-(J36-Pin_2)"), (146.41, 15.6), True),        # R168
         (("GND", "PWR_HOLD"), (128.8, 12.1), False),               # R173
         (("+3V3", "BTN_SNS"), (143.91, 9.3), True),                # R174
         (("Net-(R172-Pad2)", "PWR_HOLD"), (128.77, 9.74), False)]  # R172
SS_B_VIA = (135.2, 7.3)
V3_VIAS = {"R166": (139.775, 23.95), "R174": (142.6, 8.475)}
R173_GND_VIA = (126.75, 12.1)
SS_F = {"SS_A": [(134.62, 21.5), (134.62, 16.0), (138.32, 12.3), (138.91, 12.3)],
        "SS_B": [(137.12, 21.5), (138.9, 19.72), (138.9, 15.0), (141.41, 12.49), (141.41, 12.3)]}


def place(FP, obstacles):
    """The corner's resistors by hand (locked; U22 is placed by logic_place). Returns the references placed."""
    import power54
    from power42 import _upright
    from satellites import _box
    sheet = FP["U22"].GetSheetname()
    short = lambda p: p.GetNetname().split("/")[-1]
    done = []
    for (a, b), (x, y), upright in PARTS:
        ref = next(r for r, f in FP.items() if f.GetSheetname() == sheet and r[0] == "R" and r not in done
                   and {short(p) for p in f.Pads()} == {a, b})
        pa = next(p.GetNumber() for p in FP[ref].Pads() if short(p) == a)
        pb = next(p.GetNumber() for p in FP[ref].Pads() if short(p) == b)
        if upright:
            _upright(FP[ref], x, y, pa, pb, bottom=True)
        else:
            power54._flat_bottom(FP[ref], x, y, pa, pb)
        FP[ref].SetLocked(True)
        obstacles.append(_box(FP[ref]))
        done.append(ref)
    return done


def route(R, FP, log=print):
    """The corner's copper, planned (checked exactly)."""
    import far42
    import route_plan
    from route import B, F
    short = lambda q: q["net"].split("/")[-1]
    P = lambda ref, n: next(q for q in R.geo.pads if q["ref"] == ref and short(q) == n)
    refs = lambda a, b: next(q["ref"] for q in R.geo.pads if short(q) == a and q["ref"].startswith("R")
                             and any(short(o) == b for o in R.geo.pads if o["ref"] == q["ref"]))
    c = lambda ref, n: P(ref, n)["c"]
    segs, vias = [], []

    def lay(net, layer, pts, w=W):
        segs.extend(R.track(net, layer, pts, w))

    def via(net, xy):
        vias.append(R.via(net, *xy))

    full = lambda n: next(q["net"] for q in R.geo.pads if short(q) == n)
    ssa, ssb = full("SS_A"), full("SS_B")
    u = {q["num"]: q for q in R.geo.pads if q["ref"] == "U22"}
    j37 = {q["num"]: q["c"] for q in R.geo.pads if q["ref"] == "J37"}
    # soft-start: J38 to J37 on top; U22's SS_A along the bottom, SS_B up through a via, along the top
    lay(ssa, F, SS_F["SS_A"], W_SS)
    lay(ssb, F, SS_F["SS_B"], W_SS)
    p3, p4 = u["3"]["c"], u["4"]["c"]
    lay(ssa, B, [p3, (j37["1"][0], p3[1]), j37["1"]], W_SS)
    lay(ssb, B, [p4, SS_B_VIA], W_SS)
    via(ssb, SS_B_VIA)
    lay(ssb, F, [SS_B_VIA, (j37["2"][0], SS_B_VIA[1]), j37["2"]], W_SS)
    # PWR_HOLD: the port's via, north to R172 with R173 on the way; R172 on to U22's LED anode
    r172, r173 = refs("PWR_HOLD", "Net-(R172-Pad2)"), refs("PWR_HOLD", "GND")
    pv = (PORT_X["PWR_HOLD"], 18.4)
    via("PWR_HOLD", pv)
    h2, h3 = c(r172, "PWR_HOLD"), c(r173, "PWR_HOLD")
    lay("PWR_HOLD", B, [pv, (pv[0], h2[1] + (pv[0] - h2[0]) - 0.87), (h2[0] + 0.87, h2[1]), h2])
    lay("PWR_HOLD", B, [(pv[0], h3[1]), h3])
    g3 = c(r173, "GND")
    lay("GND", B, [g3, R173_GND_VIA], 0.4)
    via("GND", R173_GND_VIA)
    a2, a1 = c(r172, "Net-(R172-Pad2)"), u["1"]["c"]
    lay(u["1"]["net"], B, [a2, (a1[0], a2[1] - (a2[0] - a1[0])), a1])
    # BTN_SNS: R174 into J37's pin 3, its +3V3 via
    r174 = refs("BTN_SNS", "+3V3")
    lay(full("BTN_SNS"), B, [c(r174, "BTN_SNS"), j37["3"]])
    lay("+3V3", B, [c(r174, "+3V3"), V3_VIAS["R174"]], 0.4)
    via("+3V3", V3_VIAS["R174"])
    # the motor switch loop: R166 into J36.1, +3V3 via below it; the node J36.2 - R167 - R168; R168 into J37's GND
    r166, r167, r168 = refs("Net-(J36-Pin_1)", "+3V3"), refs("Net-(J36-Pin_2)", "MOTOR_OK"), \
        refs("Net-(J36-Pin_2)", "GND")
    j36 = {q["num"]: q for q in R.geo.pads if q["ref"] == "J36"}
    e166 = c(r166, "Net-(J36-Pin_1)")
    yj = j36["1"]["box"][3] - 0.5
    lay(j36["1"]["net"], B, [e166, (e166[0] + (e166[1] - yj), yj), (j36["1"]["c"][0], yj)])
    lay("+3V3", B, [c(r166, "+3V3"), V3_VIAS["R166"]], 0.4)
    via("+3V3", V3_VIAS["R166"])
    n2, k167, k168 = j36["2"]["net"], c(r167, "Net-(J36-Pin_2)"), c(r168, "Net-(J36-Pin_2)")
    lay(n2, B, [k168, j36["2"]["c"]])
    lay(n2, B, [k167, (k168[0], k167[1])])
    lay("GND", B, [c(r168, "GND"), j37["4"]], 0.4)
    mv = (PORT_X["MOTOR_OK"], 17.5)
    via("MOTOR_OK", mv)
    m7 = c(r167, "MOTOR_OK")
    lay("MOTOR_OK", B, [m7, (mv[0], m7[1] - (m7[0] - mv[0])), mv])
    bad = route_plan._check_exact(R, segs) + far42._check_vias(R, vias)
    for msg in bad[:25]:
        log(f"   power-button corner clearance: {msg}")
    if bad:
        R.failed.append("power-button corner")
    log(f"   power-button corner: {len(segs)} segments, {len(vias)} vias, {len(bad)} clearance problems")

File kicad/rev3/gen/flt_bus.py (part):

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                        bottom edge. There a via each takes them onto L3, east under the blocks' edge in the two
                        L3 lanes the edge leaves free (before the rails' legs take theirs): FLT_24 at y 49.7, just
                        under the bypass bridges' pads (JP3 / JP4), jogging between JP5's two pads; FLT_12 at
                        y 54.2, round JP5's lower pad. At the ESP32 both turn down: FLT_24 east over the top pin
                        row to its pin via, FLT_12 down beside the module to a via between the status LEDs D20 /
                        D19 and a top-side track into pin 17 (no via fits beside that pin).
  5 V                   from its test pad (TP18, right beside the module) a via down, L3 south-east, east under
                        the module and up into its pin via (it may not cross FLT_12's line: round below its via).
  42C / 42D             42C from its dive right of U17 (far42), 42D from a via west of its test pad, L3 east and north-east
                        to join FLT_5's run as a three-line bundle under the module, each peeling up into its
                        pin via in turn (FLT_5, 42C, 42D: no crossings).

The pin vias sit above the module's top pin row (outside its body), a short top-side stub into each pin. The
pull-ups hang on them on the bottom layer: FLT_24's and FLT_5's below their vias, FLT_42C's between the 5 V and
42C vias, their +3V3 ends on one 0.5 mm spine into the LDO's output cap (C103); FLT_12's below its via beside the
module; FLT_42D's below its test pad (no room at the module: U12 and C103 fill the bottom there). The pull-ups are
placed here (before the logic groups) and their room kept from the groups and the packer.
Everything is laid as planned polylines and then checked exactly, new copper against new copper too.
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SPINE_X = 139.1                                 # the pull-ups' +3V3 spine (bottom layer)
PU_V33_DX = 1.39                                # FLT_42D's pull-up: its +3V3 via this far right of its pad

# pin vias (above the top row; FLT_12's beside the module, between the LEDs D20 and D19)
PIN_VIAS = {"FLT_24": (135.3, 59.2), "FLT_5": (137.76, 59.75), "FLT_42C": (140.3, 59.75),
            "FLT_42D": (141.57, 59.75), "FLT_12": (126.25, 64.5)}

# L3 lines (from their first via on)
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
# kept for the plan's bottom-side copper (the pull-ups block their own courtyards)
KEEP = [(134.5, 57.1, 139.4, 66.7),     # the rails' pin vias, their pull-ups and the +3V3 spine
        (139.4, 57.1, 142.1, 62.7),     # the 42 V pin vias and FLT_42C's pull-up
        (122.6, 62.6, 124.4, 64.4),     # FLT_5's via beside its test pad
        (125.6, 63.9, 127.0, 65.2),     # FLT_12's via beside the module
        (109.9, 73.9, 111.7, 76.8),     # the 42 V lines' vias (42C's dive sits in far42's keep)
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        assert math.dist(pts[-1], (vx, vy)) < 1e-6, f"FLT bus: {net} ends off its pin via"
        via(net, vx, vy)
        px, py = c("U13", pin)
        if net == "FLT_12":                    # between D20 and D19, along the module's pin column
            lay(net, F, [(vx, vy), (128.7, vy), (128.7, py), (px, py)])
        elif abs(px - vx) > 1e-6:              # a 45-degree jog to the pin, then straight in
            lay(net, F, [(vx, vy), (px, vy + abs(vx - px)), (px, py)])
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            lay("+3V3", B, [(ux, uy), (ux + PU_V33_DX, uy)], SW)
        else:
            lay(net, B, [(vx, vy), (fx, fy)])
    # the +3V3 spine: FLT_42C's pull-up down to the rails' pull-ups, with a branch into C103's +3V3 pad
    (ax, ay), (bx, by), (cx, cy) = (c(rl[n][1], "1") for n in ("FLT_42C", "FLT_5", "FLT_24"))
    lay("+3V3", B, [(ax, ay), (ax, by - 0.5), (ax - 0.5, by), (cx, by)], SW)
    c103 = next(p for p in R.geo.pads if p["ref"] == "C103" and p["net"] == "+3V3")["c"]
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
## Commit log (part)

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2024-10-10 v2.0.2
2024-10-11 added status leds
2024-11-01 changed i2c connection
2024-11-01 added spi and i2c terminals
2024-11-01 sync
2024-12-02 Remove unused switch on the battery rail
2024-12-03 Add LTC7004 driver
2024-12-03 iterate the layoutL
2024-12-05 fix the layout
2024-12-06 change input mosfet for a supported one
2024-12-13 Finish the design
2024-12-16 v2.2.0
2024-12-21 add base resistors for the power mosfets
2024-12-21 change shunt value
2024-12-21 Adjust resistor and transil values
2024-12-21 update bom
2024-12-28 remove solder mask from high current traces and optimize vias for cheaper manufacturing process
2025-01-23 safety features added, uart connector added
2025-01-28 Add first firmware version
2025-06-16 Add dV/dt for inrush current limitation on the main power line
2025-06-19 finish inrush current limiting
2025-06-20 finish v2.4.0
2025-06-20 rework the 5V switching
2025-06-24 adjust component values
2026-03-15 Add files via upload
    - Použitie normovaných hodnôt súčiastok v dizajne
    Opravený typ diód a hodnota D9,D10,D11,D14.
    Opravená orientácia diód D9, D10, D11, D14.
    - Zmeny hodnôt komponentov
    Opravene hodnoty komponentov:
    5,5nF -> 5,6nF
2026-03-15 Generate gerber production files
